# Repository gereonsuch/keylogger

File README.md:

# Hardware Keylogger — Academic Research Project

> **⚠️ LEGAL DISCLAIMER**
> Please read the [Disclaimer](#disclaimer) section in full before using anything in this repository.

---

## Table of Contents

- [Project Description](#project-description)
- [Academic Context](#academic-context)
- [Hardware](#hardware)
- [Software](#software)
- [Licenses](#licenses)
- [Disclaimer](#disclaimer)

---

## Project Description

This repository contains schematics, layout files, and firmware for a hardware keylogger developed as part of an academic thesis. 

The device is designed exclusively for **controlled laboratory environments and explicitly authorized penetration tests**.

---

## Academic Context

This project is part of the following academic work:

| | |
|---|---|
| **Title** | USB Keylogging from scratch |
| **Author** | Gereon Such |
| **Institution** | Wilhelm Büchner Hochschule |
| **Supervisor** | Michael Fleury |
| **Submitted** | May 2026 |

---

## Hardware

There are multiple schematics in this project:

- USB Feedthrough and daughterboard for Rsapberry Pi PICO2 board under hardware/pico2daughterboard
- Full custom Keylogger board with RP235x microcontroller under hardware/full_rp2350_keylogger
  Since some of the components suggested by the Raspberry Pi hardware guide do not have an equivalent footprint in the KiCAD base library. There is a script to clone these components to the project directory, which should be done before loading the schematic. Nonetheless, you can select footprints yourself, but this will most propably invalidate the pcb design.

### Hardware License

All hardware design files (schematics, PCB layout, BOM) are released under the
**CERN Open Hardware Licence Version 2 — Strongly Reciprocal (CERN-OHL-S v2)**.
See [`hardware/LICENSE`](hardware/LICENSE).

---

## Software

### Directory Structure
```
firmware/
├── src/              # Source code
├── platformio.ini    # Project configuration
├── build.sh          # Build script for compilation and flashing
└── LICENSE           # Software license for all firmware files
```

### Software License

All source code is released under the **GNU General Public License v3.0 (GPL-3.0)**.
See [`firmware/LICENSE`](firmware/LICENSE).

---

## Licenses

| Component | License |
|---|---|
| Firmware / Software | [GPL-3.0](firmware/LICENSE) |
| Hardware Design | [CERN-OHL-S v2](hardware/LICENSE) |
| Documentation | [CC BY-SA 4.0](https://creativecommons.org/licenses/by-sa/4.0/) |

Both the GPL-3.0 and CERN-OHL-S v2 are **strong copyleft licenses**: any derivative work must be released under the same terms.

---

## Disclaimer

This project was developed solely for **academic and scientific research purposes** under institutional supervision. It is intended exclusively for use in **authorized and controlled test environments**.

### Authorized Use Only

Using this device or any part of this software on systems, devices, or networks **without the explicit prior consent of the owner is illegal**. Unauthorized deployment may constitute a criminal offence under German law, including but not limited to:

| Statute | Offence |
|---|---|
| **§ 202a StGB** | *Ausspähen von Daten* — Unauthorized access to protected data |
| **§ 202b StGB** | *Abfangen von Daten* — Interception of data |
| **§ 303a StGB** | *Datenveränderung* — Unlawful alteration of data |
| **§ 303b StGB** | *Computersabotage* — Computer sabotage |

Depending on your jurisdiction, equivalent or additional statutes may apply. It is your sole responsibility to ensure that any use of this project complies with all applicable local, national, and international laws.

### No Liability

The authors, contributors, and affiliated institution of this project accept **no liability whatsoever** for any damages, data loss, legal consequences, or other harm arising from the use, misuse, or inability to use this project or any of its components. This includes, but is not limited to, direct, indirect, incidental, or consequential damages.

This software and hardware are provided **"as is"**, without warranty of any kind, express or implied.

### Responsible Disclosure

This project is published in the spirit of **responsible disclosure** and to advance the scientific and academic discourse on hardware security. The authors explicitly condemn any malicious, unauthorized, or otherwise unlawful use of the concepts, designs, or code contained in this repository.

---

*For questions regarding authorized use or the academic context of this project, please contact me via https://suchdsp.com*

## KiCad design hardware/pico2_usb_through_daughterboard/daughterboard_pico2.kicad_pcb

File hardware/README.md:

# Hardware Keylogger — Academic Research Project

> **⚠️ LEGAL DISCLAIMER**
> Please read the [Disclaimer](#disclaimer) section in full before using anything in this repository.

---

## Subprojects

I tried different setups during the design process. This folder contains the relevant ones.

- pico2_usb_through_daughterboard
  This is a daughterboard for the Pico2 board you can commonly purchase. Since this PCB is pretty minimalistic, you can also choose to just implement on a perfboard or stripboard. 
  - /pico2_usb_through_daughterboard contains the kicad project including production files
  - /pico2_usb_through_daughterboard__gerber.zip contains the gerber files for jlcpcb production without any components

- full_keylogger_rp2354
  This is the full keylogger including on board SD card holder, power supply and quartz oscillator and USB in/out and USB debug connector. 
  This layout is very condensed, just as a keylogger should be ;) Maybe I design stl files for a 3d printable enclosing in the near future...
  As the pushbuttons are optional and the USB-A connectors are easily solderable by hand, they are left out in the production files. 
  - /full_keylogger_rp2354 contains the kicad project. be aware, that some footprints are custom from eda files. you will need to clone these with your preferred method. LCSC numbers for the parts are added
  - /full_keylogger_rp2354__only_top_components__gerber.zip contains all gerber files for PCB production for TOPSIDE assembly only. This reduces cost massively as only one side of the board needs to be assembled and the SD card is optional anyways.
  - /full_keylogger_rp2354__only_top_components__BOM.csv contains the material list of all TOPSIDE components
  - /full_keylogger_rp2354__only_top_components__CPL.csv contains the component placement of all TOPSIDE components
  - /full_keylogger_rp2354__gerber.zip contains all gerber files for PCB production for production. This is the dual side assembly, which is slightly more costly
  - /full_keylogger_rp2354__BOM.csv contains the material list for DUAL SIDE PLACEMENT components
  - /full_keylogger_rp2354__CPL.csv contains the component placement for DUAL SIDE PLACEMENT components
  
___!!! Be aware, that some component placements like the power regulator and the inductivity need to be rotated at JLCPCB production !!!___

---

## Hardware License

All hardware design files (schematics, PCB layout, BOM) are released under the
**CERN Open Hardware Licence Version 2 — Strongly Reciprocal (CERN-OHL-S v2)**.
See [`hardware/LICENSE`](hardware/LICENSE).

---

## Disclaimer

This project was developed solely for **academic and scientific research purposes** under institutional supervision. It is intended exclusively for use in **authorized and controlled test environments**.

### Authorized Use Only

Using this device or any part of this software on systems, devices, or networks **without the explicit prior consent of the owner is illegal**. Unauthorized deployment may constitute a criminal offence under German law, including but not limited to:

| Statute | Offence |
|---|---|
| **§ 202a StGB** | *Ausspähen von Daten* — Unauthorized access to protected data |
| **§ 202b StGB** | *Abfangen von Daten* — Interception of data |
| **§ 303a StGB** | *Datenveränderung* — Unlawful alteration of data |
| **§ 303b StGB** | *Computersabotage* — Computer sabotage |

Depending on your jurisdiction, equivalent or additional statutes may apply. It is your sole responsibility to ensure that any use of this project complies with all applicable local, national, and international laws.

### No Liability

The authors, contributors, and affiliated institution of this project accept **no liability whatsoever** for any damages, data loss, legal consequences, or other harm arising from the use, misuse, or inability to use this project or any of its components. This includes, but is not limited to, direct, indirect, incidental, or consequential damages.

This software and hardware are provided **"as is"**, without warranty of any kind, express or implied.

### Responsible Disclosure

This project is published in the spirit of **responsible disclosure** and to advance the scientific and academic discourse on hardware security. The authors explicitly condemn any malicious, unauthorized, or otherwise unlawful use of the concepts, designs, or code contained in this repository.

---

*For questions regarding authorized use or the academic context of this project, please contact me via https://suchdsp.com*

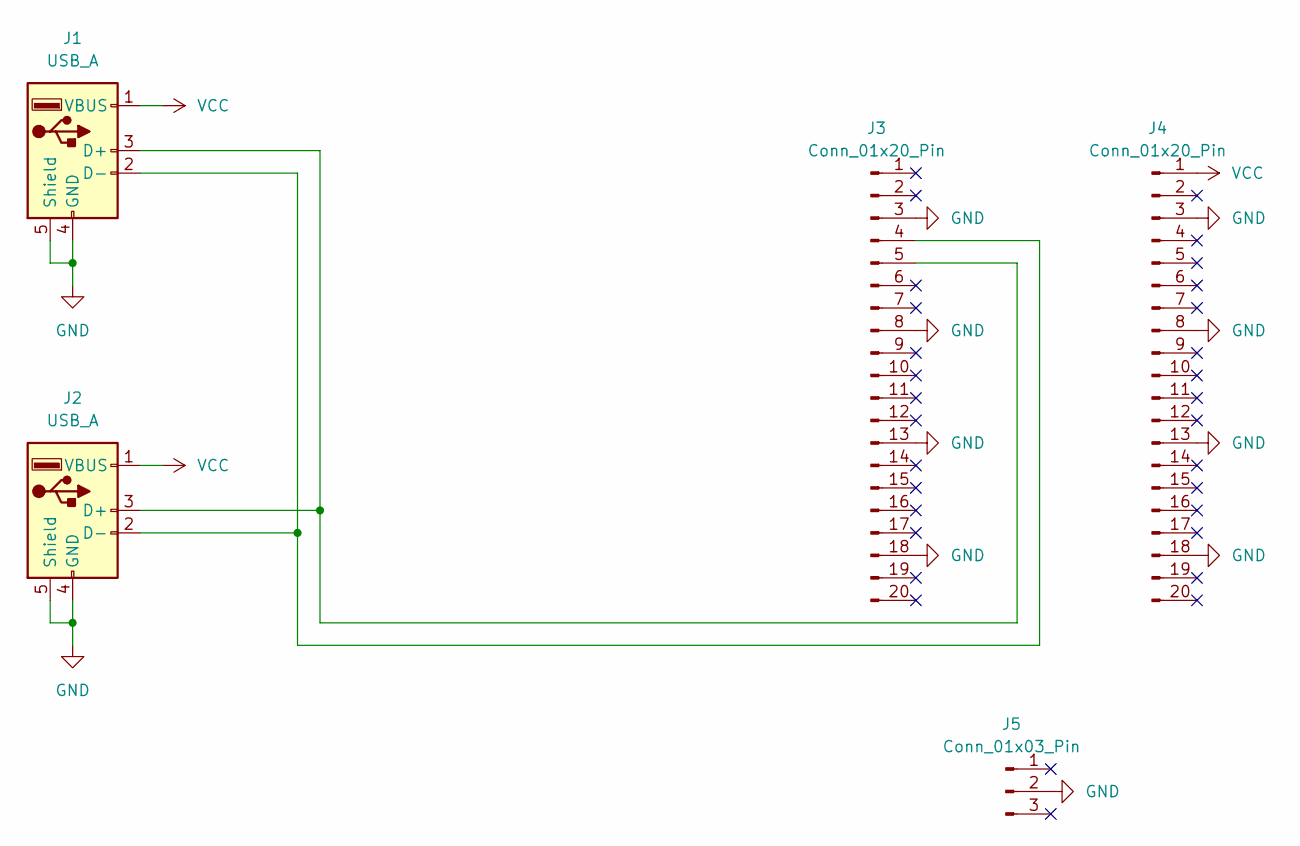
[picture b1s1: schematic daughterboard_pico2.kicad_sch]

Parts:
J1: USB_A; USB_A_Molex_67643_Horizontal
J2: USB_A; usb_conn_throughhole_aliexpress
J3, J4: Conn_01x20_Pin; PinSocket_1x20_P2.54mm_Vertical
J5: Conn_01x03_Pin; PinSocket_1x03_P2.54mm_Vertical

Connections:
GND: J1.4 (GND), J1.5 (Shield), J2.4 (GND), J2.5 (Shield), J3.3, J3.8, J3.13, J3.18, J4.3, J4.8, J4.13, J4.18, J5.2
unnamed: J1.3 (D+), J2.3 (D+), J3.5
unnamed: J1.2 (D-), J2.2 (D-), J3.4
VCC: J1.1 (VBUS), J2.1 (VBUS), J4.1

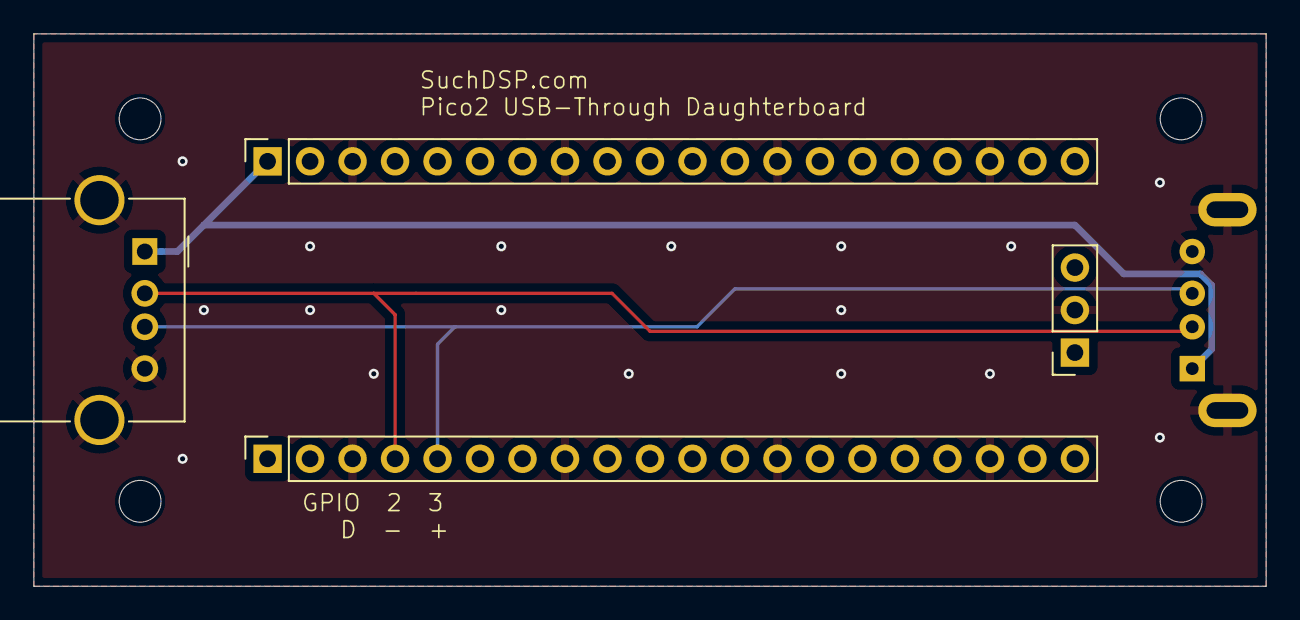
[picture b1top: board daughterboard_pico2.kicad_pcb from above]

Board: 2 copper layers, 73.7 x 33.0 mm, 5 parts (0 on the bottom side), 4 nets.

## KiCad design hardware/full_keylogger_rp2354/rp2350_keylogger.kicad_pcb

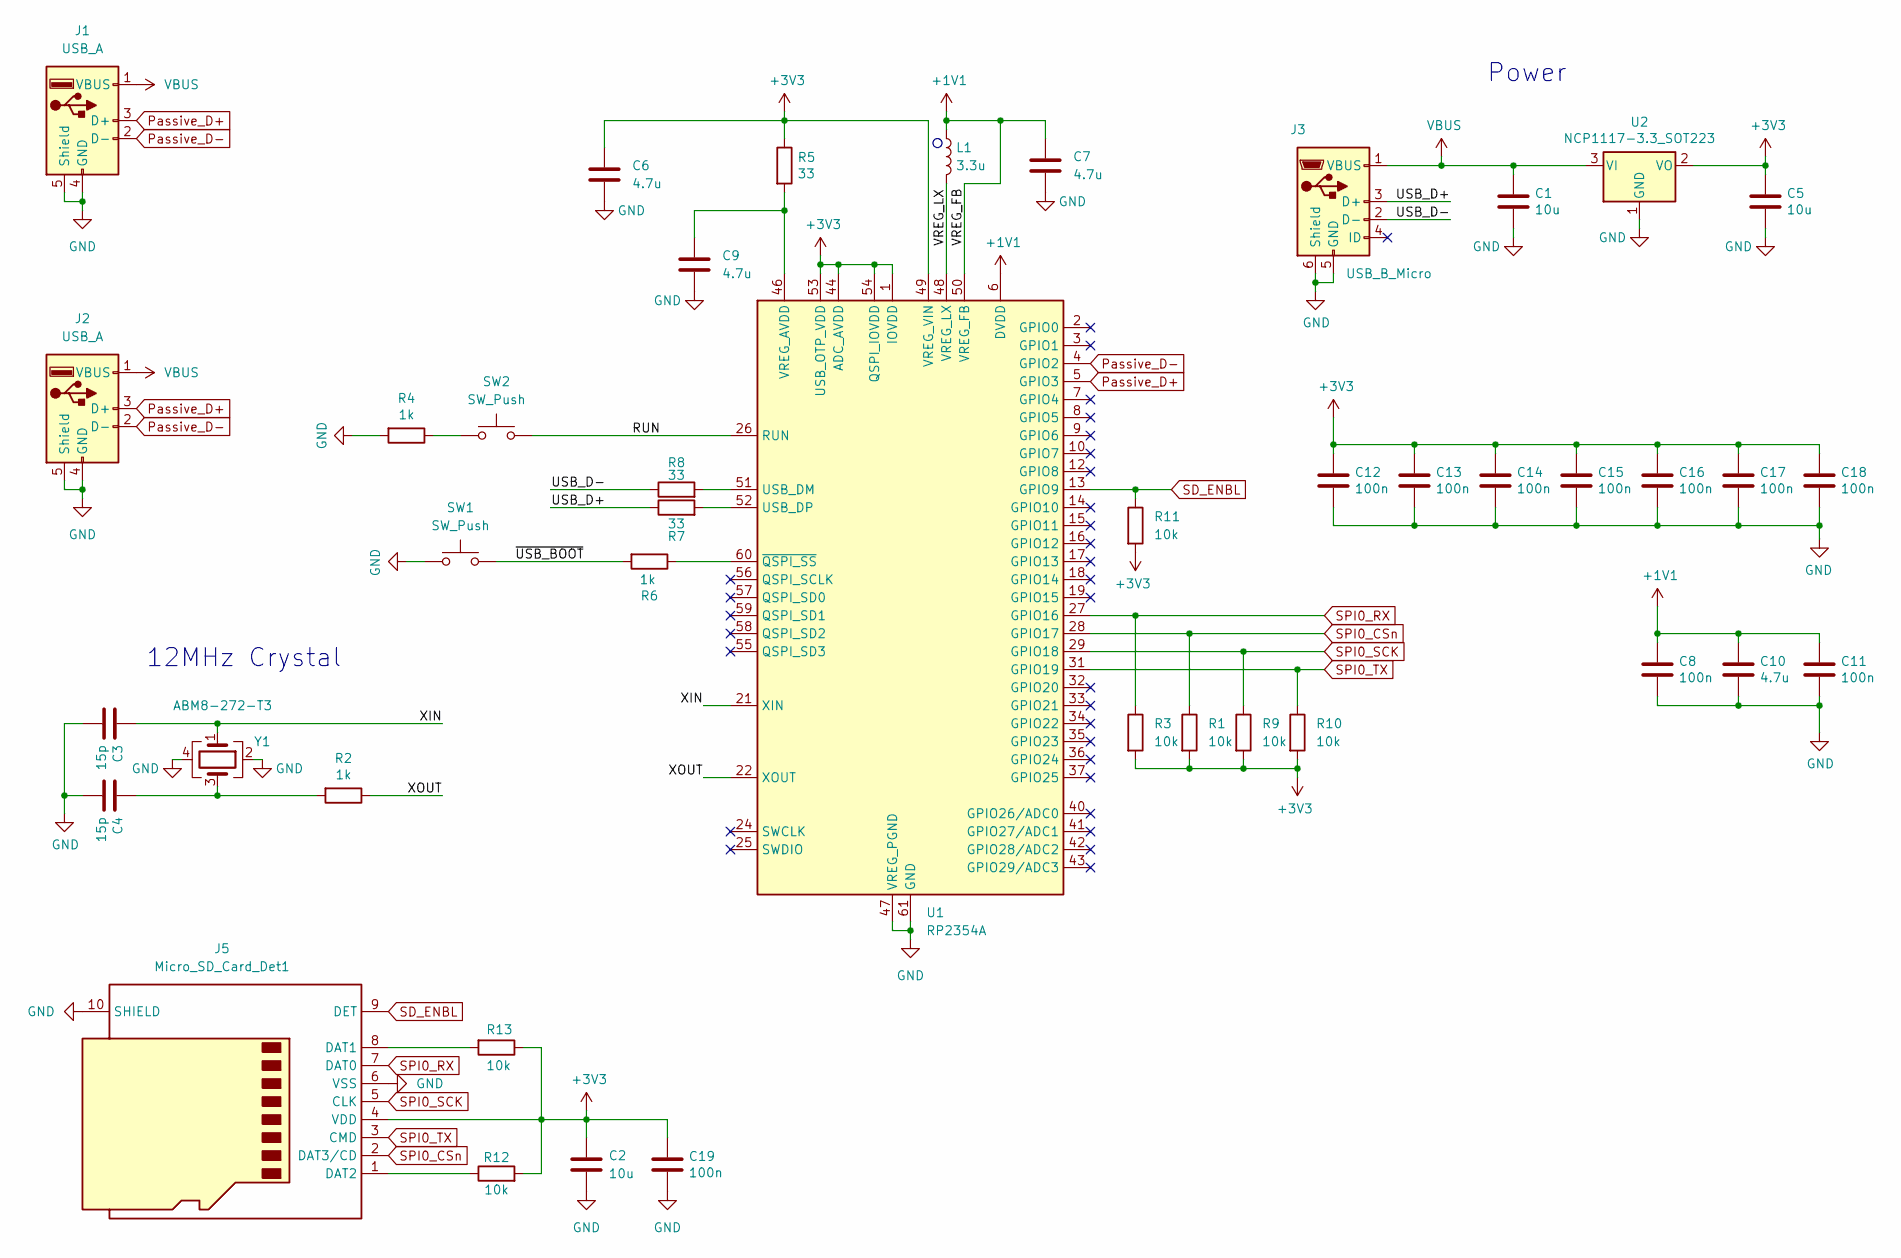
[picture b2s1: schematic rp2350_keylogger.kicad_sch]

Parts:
C1, C2, C5: 10u; C_0805_2012Metric; LCSC C15850
C3, C4: 15p; C_0402_1005Metric; LCSC C1548
C6, C7: 4.7u; C_0402_1005Metric_small_pads; LCSC C23733
C8, C11, C12, C13, C14, C15, C16, C17, C18, C19: 100n; C_0402_1005Metric; LCSC C1525
C9, C10: 4.7u; C_0402_1005Metric; LCSC C23733
J1: USB_A; USB_A_Molex_67643_Horizontal
J2: USB_A; usb_conn_throughhole_aliexpress
J3: USB_B_Micro; USB_Micro-B_Amphenol_10118193-0001LF_Horizontal; LCSC C132562
J5: Micro_SD_Card_Det1; TF-SMD_TF-015; LCSC C113206
L1: 3.3u; L_pol_2016; LCSC C42411119
R1, R3, R9, R10, R11, R12, R13: 10k; R_0402_1005Metric; LCSC C25744
R2, R4, R6: 1k; R_0402_1005Metric; LCSC C11702
R5, R7, R8: 33; R_0402_1005Metric; LCSC C25105
SW1, SW2: SW_Push; SW_Push_1P1T_NO_Vertical_Wuerth_434133025816
U1: RP2354A; QFN-60-1EP_7x7mm_P0.4mm_EP3.4x3.4mm; LCSC C41378174
U2: NCP1117-3.3_SOT223; SOT-223-3_TabPin2; LCSC C146799
Y1: ABM8-272-T3; Crystal_SMD_3225-4Pin_3.2x2.5mm; LCSC C20625731

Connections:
+1V1: C7.1, C8.1, C10.1, C11.1, L1.1, U1.6 (DVDD), U1.23 (DVDD), U1.39 (DVDD), U1.50 (VREG_FB)
+3V3: C2.1, C5.1, C6.1, C12.1, C13.1, C14.1, C15.1, C16.1, C17.1, C18.1, C19.1, J5.4 (VDD), R1.2, R3.2, R5.1, R9.2, R10.2, R11.2, R12.2, R13.1, U1.1 (IOVDD), U1.11 (IOVDD), U1.20 (IOVDD), U1.30 (IOVDD), U1.38 (IOVDD), U1.44 (ADC_AVDD), U1.45 (IOVDD), U1.49 (VREG_VIN), U1.53 (USB_OTP_VDD), U1.54 (QSPI_IOVDD), U2.2 (VO)
/RUN: SW2.2, U1.26 (RUN)
/USB_D+: J3.3 (D+), R7.1
/USB_D-: J3.2 (D-), R8.1
/VREG_LX: L1.2, U1.48 (VREG_LX)
/XIN: C3.1, U1.21 (XIN), Y1.1
/XOUT: R2.1, U1.22 (XOUT)
/~USB_BOOT: R6.2, SW1.2
GND: C1.2, C2.2, C3.2, C4.2, C5.2, C6.2, C7.2, C8.2, C9.2, C10.2, C11.2, C12.2, C13.2, C14.2, C15.2, C16.2, C17.2, C18.2, C19.2, J1.4 (GND), J1.5 (Shield), J2.4 (GND), J2.5 (Shield), J3.5 (GND), J3.6 (Shield), J5.6 (VSS), J5.10 (SHIELD), J5.11, J5.12, J5.13, R4.2, SW1.1, U1.47 (VREG_PGND), U1.61 (GND), U2.1 (GND), Y1.2, Y1.4
unnamed: C4.1, R2.2, Y1.3
unnamed: J5.8 (DAT1), R13.2
unnamed: J5.1 (DAT2), R12.1
unnamed: R4.1, SW2.1
unnamed: R8.2, U1.51 (USB_DM)
unnamed: R7.2, U1.52 (USB_DP)
unnamed: C9.1, R5.2, U1.46 (VREG_AVDD)
unnamed: R6.1, U1.60 (~QSPI_SS)
Passive_D+: J1.3 (D+), J2.3 (D+), U1.5 (GPIO3)
Passive_D-: J1.2 (D-), J2.2 (D-), U1.4 (GPIO2)
SD_ENBL: J5.9 (DET), R11.1, U1.13 (GPIO9)
SPI0_CSn: J5.2 (DAT3/CD), R1.1, U1.28 (GPIO17)
SPI0_RX: J5.7 (DAT0), R3.1, U1.27 (GPIO16)
SPI0_SCK: J5.5 (CLK), R9.1, U1.29 (GPIO18)
SPI0_TX: J5.3 (CMD), R10.1, U1.31 (GPIO19)
VBUS: C1.1, J1.1 (VBUS), J2.1 (VBUS), J3.1 (VBUS), U2.3 (VI)

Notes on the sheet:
Power
12MHz Crystal

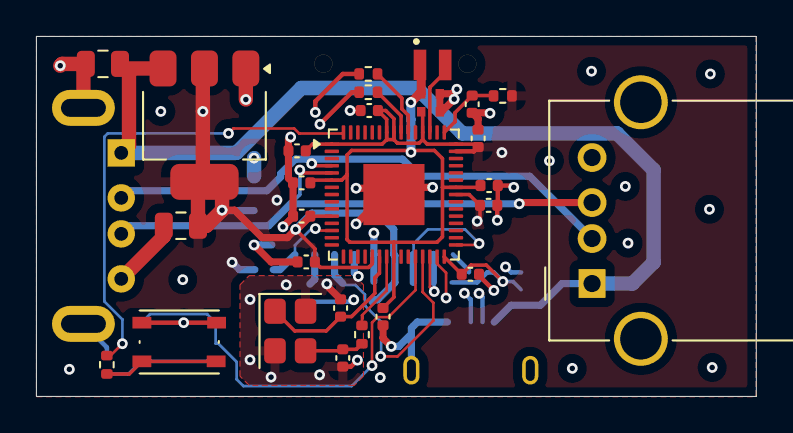
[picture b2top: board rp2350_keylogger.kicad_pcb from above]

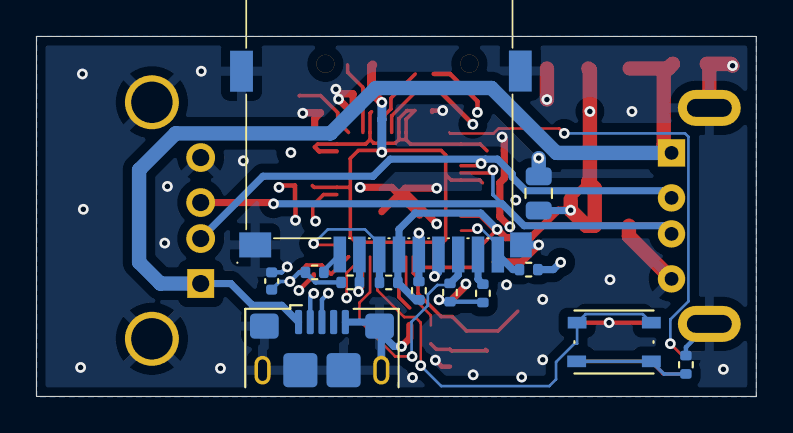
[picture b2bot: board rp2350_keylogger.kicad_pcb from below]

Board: 4 copper layers, 40.0 x 20.0 mm, 42 parts (13 on the bottom side), 26 nets.

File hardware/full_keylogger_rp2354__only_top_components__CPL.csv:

Designator,Val,Package,Mid X,Mid Y,Rotation,Layer
C1,10u,C_0805_2012Metric,101.0768,-76.5556,180.0,top
C10,4.7u,C_0402_1005Metric,116.6368,-90.5992,-90.0,top
C11,100n,C_0402_1005Metric,122.5328,-83.3144,0.0,top
C12,100n,C_0402_1005Metric,115.8728,-79.1464,180.0,top
C13,100n,C_0402_1005Metric,111.8648,-81.3864,180.0,top
C14,100n,C_0402_1005Metric,122.5048,-84.4144,0.0,top
C15,100n,C_0402_1005Metric,112.1188,-85.0144,180.0,top
C16,100n,C_0402_1005Metric,121.4888,-88.2444,0.0,top
C17,100n,C_0402_1005Metric,121.92,-80.6932,90.0,top
C18,100n,C_0402_1005Metric,112.3716,-87.5584,180.0,top
C19,100n,C_0402_1005Metric,124.3076,-88.618,90.0,bottom
C2,10u,C_0805_2012Metric,109.474,-83.754,90.0,bottom
C3,15p,C_0402_1005Metric,114.2792,-90.1164,90.0,top
C4,15p,C_0402_1005Metric,114.4016,-92.8924,-90.0,top
C5,10u,C_0805_2012Metric,105.41,-85.5472,180.0,top
C6,4.7u,C_0402_1005Metric_small_pads,119.2758,-79.2144,0.0,top
C7,4.7u,C_0402_1005Metric_small_pads,119.2758,-78.2144,0.0,top
C8,100n,C_0402_1005Metric,112.1188,-83.1644,180.0,top
C9,4.7u,C_0402_1005Metric,121.5908,-78.7944,-90.0,top
J1,USB_A,USB_A_Molex_67643_Horizontal,129.9574,-85.2592,90.0,top
J2,USB_A,usb_conn_throughhole_aliexpress,100.55,-85.0,-90.0,top
J3,USB_B_Micro,USB_Micro-B_Amphenol_10118193-0001LF_Horizontal,121.5156,-92.3736,0.0,bottom
J5,Micro_SD_Card_Det1,TF-SMD_TF-015,118.239,-81.9805,180.0,bottom
L1,3.3u,L_pol_2016,119.3908,-76.6144,0.0,top
R1,10k,R_0402_1005Metric,119.9408,-88.6948,180.0,bottom
R10,10k,R_0402_1005Metric,117.8072,-88.6968,0.0,bottom
R11,10k,R_0402_1005Metric,110.0308,-87.9856,0.0,bottom
R12,10k,R_0402_1005Metric,121.92,-88.138,180.0,bottom
R13,10k,R_0402_1005Metric,112.5728,-89.3044,90.0,bottom
R2,1k,R_0402_1005Metric,115.4684,-91.5944,-90.0,top
R3,10k,R_0402_1005Metric,114.4016,-89.2576,270.0,bottom
R4,1k,R_0402_1005Metric,101.2952,-93.2708,90.0,bottom
R5,33,R_0402_1005Metric,123.2896,-78.3336,180.0,top
R6,1k,R_0402_1005Metric,101.2952,-93.2708,-90.0,top
R7,33,R_0402_1005Metric,115.822,-78.1304,0.0,top
R8,33,R_0402_1005Metric,115.822,-77.1144,0.0,top
R9,10k,R_0402_1005Metric,116.1288,-89.152,270.0,bottom
SW1,SW_Push,SW_Push_1P1T_NO_Vertical_Wuerth_434133025816,105.3162,-92.007,0.0,top
SW2,SW_Push,SW_Push_1P1T_NO_Vertical_Wuerth_434133025816,105.2904,-92.007,180.0,bottom
U1,RP2354A,QFN-60-1EP_7x7mm_P0.4mm_EP3.4x3.4mm,117.2408,-83.8144,0.0,top
U2,NCP1117-3.3_SOT223,SOT-223-3_TabPin2,106.7168,-79.9596,-90.0,top
Y1,ABM8-272-T3,Crystal_SMD_3225-4Pin_3.2x2.5mm,111.4852,-91.3964,-90.0,top

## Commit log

2026-05-09 base firmware. specific readme pending.
2026-05-09 hardware components added
2026-05-09 measurement and analysis files.
